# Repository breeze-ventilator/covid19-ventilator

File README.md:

#  Breeze Ventilator
Welcome to our open-source, low-cost ventilator design! We are a group of students, physicians and engineers who worked on the design to help alleviate the critical need for ventilators during the COVID-19 pandemic.

Here is a [video](https://youtu.be/5ufh_80dSsk) with an overview of our design.

<p align="center">
  
</p>

You can also check out our [in depth design video](https://youtu.be/dRpsoaCI0QA) and [public announcement video](https://youtu.be/4-jjhEgUjkQ).

## Operational Diagram

## Folder Structure
**Mechanical:** Everything you need to construct the device including the bill of materials and the CAD files.

**Software:** Breeze ventilator code including code for both the interface (running on the Raspberry Pi 4) and the firmware (running on the Arduino Mega).

**Electronics:** PCBs and the circuit diagrams.

**Documentation:** Documentation for operating the device including the User Guide and the Assembly guide, which will help you set-up and run your device smoothly.

## Conclusion

The Breeze Ventilator was built during a design sprint and is not ready to be safely used as a functioning ventilator. Nevertheless, we hope that you will find inspiration from our design and that it will help you with your projects! 

If you have any comments, questions or suggestions you can reach out to our team through raphael.hotter@mail.mcgill.ca

Good luck with your projects and happy creating!

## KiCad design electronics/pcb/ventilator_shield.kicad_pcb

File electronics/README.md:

# Electrical
* `pcb` folder contains KiCad files.
* `parts` folder contains datasheets of off-the-shelf parts.
* `Electrical diagram.pdf` is a simplified diagram of the electronics/
* `Diagram as sent for quote.pdf` is the diagram of the pcb as used.
* `Board Specifications.pdf` contains calculations for the design of the pcb

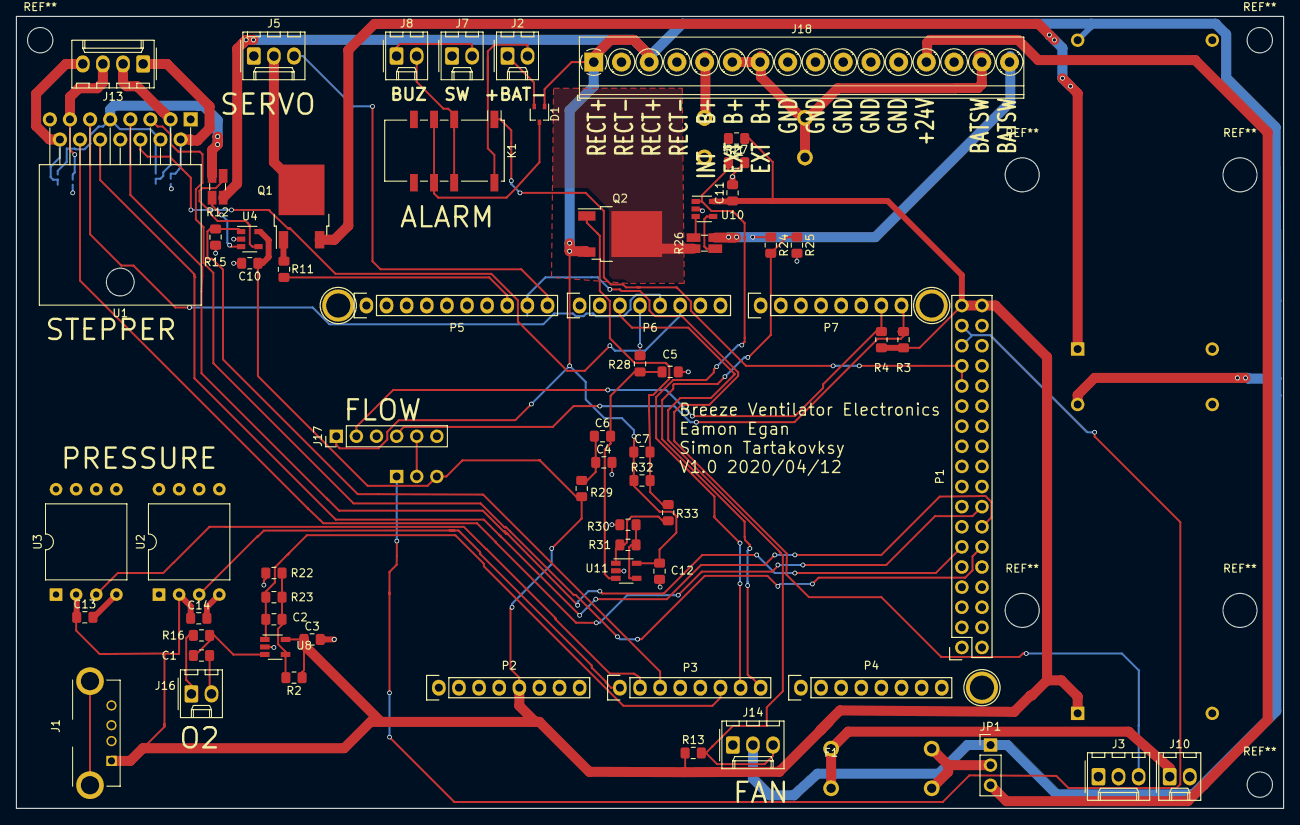
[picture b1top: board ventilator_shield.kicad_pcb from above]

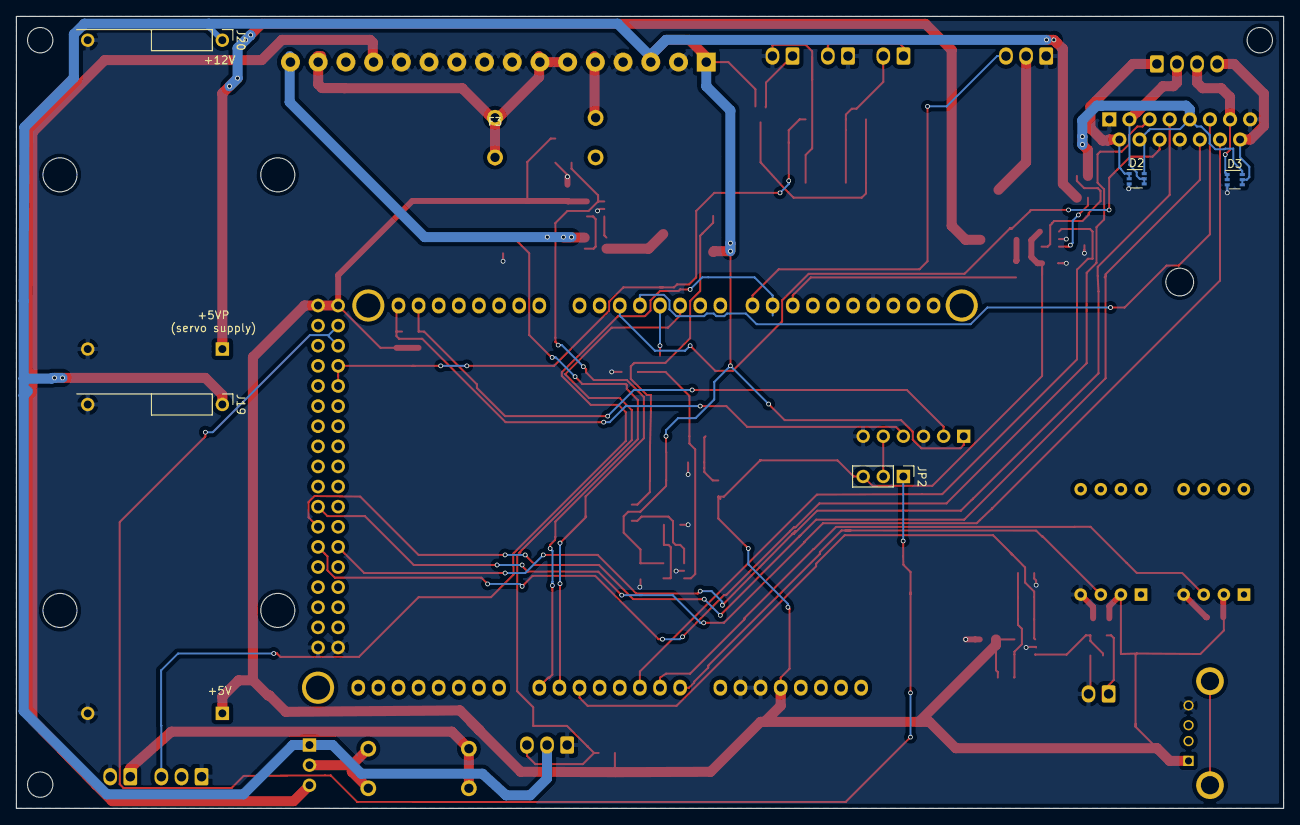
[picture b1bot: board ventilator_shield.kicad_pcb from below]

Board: 2 copper layers, 160.0 x 100.0 mm, 74 parts (6 on the bottom side), 56 nets.

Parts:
C1, C2, C3, C4, C5, C6, C7, C10, C11, C12, C13, C14: C; C_0805_2012Metric_Pad1.15x1.40mm_HandSolder
D1: BAV70W; SOT-323_SC-70
D2, D3: BAV756S; SOT-363_SC-70-6
F1, F3: Fuse; LittelFuse_clips_01110501Z_10mm_fuse
J1: USB_A; USB_A_TE_Connectivity_292303-1
J2, J7, J8, J10, J16: Conn_01x02; Molex_KK-254_AE-6410-02A_1x02_P2.54mm_Vertical
J3, J5, J14: Conn_01x03; Molex_KK-254_AE-6410-03A_1x03_P2.54mm_Vertical
J13: Conn_01x04; Molex_KK-254_AE-6410-04A_1x04_P2.54mm_Vertical
J17: Conn_01x06_Male; PinHeader_1x06_P2.54mm_Vertical
J18: Screw_Terminal_01x16; TerminalBlock_Phoenix_PT-1,5-16-3.5-H_1x16_P3.50mm_Horizont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
J19, J20: Conn_01x04; Buck_Converter_Module
JP1, JP2: Jumper_3_Open; PinHeader_1x03_P2.54mm_Vertical
K1: G6S-2; Relay_DPDT_Omron_G6S-2F
P1: Digital; Socket_Strip_Arduino_2x18
P2: Power; Socket_Strip_Arduino_1x08
P3, P4: Analog; Socket_Strip_Arduino_1x08
P5: PWM; Socket_Strip_Arduino_1x10
P6: PWM; Socket_Strip_Arduino_1x08
P7: Communication; Socket_Strip_Arduino_1x08
P10, P11, P13: CONN_01X01; Arduino_1pin
Q1, Q2: SUD19P06-60; TO-252-2
R1, R2, R11, R15, R16, R22, R23, R27: R_US; R_0805_2012Metric_Pad1.15x1.40mm_HandSolder
R3, R4: 4K7; R_0805_2012Metric_Pad1.15x1.40mm_HandSolder
R12, R26: LVK12R010FER; R_Shunt_Ohmite_LVK12
R13: 1K; R_0805_2012Metric_Pad1.15x1.40mm_HandSolder
R24, R28, R29, R31, R33: 20K; R_0805_2012Metric_Pad1.15x1.40mm_HandSolder
R25, R30, R32: 10K; R_0805_2012Metric_Pad1.15x1.40mm_HandSolder
U1: L298HN; TO-220-15_P2.54x2.54mm_StaggerOdd_Lead5.84mm_TabDown
U2, U3: HSCDLND001PGAA5; DIP-8_W13.3mm
U4, U10: INA138; SOT-23-5
U8, U11: OPA188xxDBV; TSOT-23-5

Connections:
+5V: C3.1, C10.1, C11.1, C13.1, C14.1, J1.1, J19.1, JP2.3, P1.35, P1.36, P2.5, R1.1, R2.1, R3.1, R4.1, R13.1, R29.2, U2.2, U3.2, U4.5, U8.5, U10.5
+5VP: J20.1, Q1.3
+12V: C7.1, C12.1, D1.1, J14.2, J17.1, J18.1, J18.3, J19.2, J20.2, JP1.1, Q2.3, R12.1, R32.1, U11.5
+24V: J18.13, JP1.3
/Sheet5E8D3A49/ALARM_OFF: K1.1, P1.27, P1.29
/Sheet5E8D3A49/ESC_PWM1: J3.3, P5.9
/Sheet5E8D3A49/EnA: P6.6, U1.6
/Sheet5E8D3A49/EnB: P6.5, U1.11
/Sheet5E8D3A49/FAN_TACH: J14.3, P6.3, R13.2
/Sheet5E8D3A49/IN1: P1.12, U1.5
/Sheet5E8D3A49/IN2: P1.11, U1.7
/Sheet5E8D3A49/IN3: P1.14, U1.10
/Sheet5E8D3A49/IN4: P1.16, U1.12
/Sheet5E8D3A49/SERVO_OFF: P5.8, R11.2
/Sheet5E8D3A49/SERVO_PWM1: J5.3, P5.10
/Sheet5E8D3A49/STEPPER_CURRENT: P3.3, R15.1, U4.1
/Sheet5E8D3A49/p_5: J5.2, Q1.2
/Sheet5E8D3A49/p_6: D2.1, D2.2, J13.1, U1.2
/Sheet5E8D3A49/p_7: D2.4, D2.5, J13.2, U1.3
/Sheet5E8D3A49/p_8: D3.1, D3.2, J13.3, U1.13
/Sheet5E8D3A49/p_9: D3.4, D3.5, J13.4, U1.14
/Sheet5E8D3A49/p_10: F1.2, JP1.2
/Sheet5E8D3A49/p_11: F1.1, J10.1
/Sheet5E8D3A49/p_13: D2.6, D3.6, R12.4, U1.4, U1.9
/Sheet5E9ADB54/FLOW-SCL: J17.4, P7.8, R3.2
/Sheet5E9ADB54/FLOW-SDA: J17.2, P7.7, R4.2
/Sheet5E9ADB54/FLOWSENSOR_POWER: JP2.1, P1.31, P1.33
/Sheet5E9ADB54/O2SENSOR_OUT: C2.1, P3.6, R23.1, U8.1
/Sheet5E9ADB54/PRESSURE_A: P3.1, U2.3
/Sheet5E9ADB54/PRESSURE_B: P3.2, U3.3
/Sheet5EAFE470/BATT_CHARGE_CTRL: P6.4, R28.2
/Sheet5EAFE470/p_1: F3.2, J18.5
/Sheet5EAFE470/p_2: F3.1, J18.6, J18.7, J18.15
/Sheet5EAFE470/p_3: J18.16, R24.1, R26.4
/Sheet5EAFE470/p_4: Q2.2, R26.1
/arduino_mega/BATMON_CUR: P3.7, R1.2, R27.1, U10.1
/arduino_mega/BATMON_VLT: P3.8, R24.2, R25.1
GND: C1.2, C3.2, C4.2, C5.2, C10.2, C11.2, C12.2, C13.2, C14.2, D2.3, D3.3, J1.4, J2.2, J3.1, J5.1, J7.1, J10.2, J14.1, J16.2, J17.3, J17.6, J18.2, J18.4, J18.8, J18.9, J18.10, J18.11, J18.12, J19.3, J19.4, J20.3, J20.4, K1.12, P1.1, P1.2, P2.6, P2.7, P5.4, R15.2, R22.2, R25.2, R27.2, R30.2, U1.1, U1.8, U1.15, U2.4, U3.4, U4.2, U8.2, U10.2, U11.2
unnamed: C1.1, R16.1, U8.3
unnamed: C2.2, R2.2, R22.1, R23.2, U8.4
unnamed: C4.1, C6.1, R29.1
unnamed: C5.1, C6.2, R28.1, U11.3
unnamed: C7.2, Q2.1, R32.2, R33.2
unnamed: D1.2, J2.1
unnamed: D1.3, K1.4, K1.9
unnamed: J7.2, J8.1
unnamed: J8.2, K1.3, K1.10
unnamed: J16.1, R16.2
unnamed: J17.5, JP2.2
unnamed: Q1.1, R11.1
unnamed: R12.2, U4.3
unnamed: R12.3, U4.4
unnamed: R26.2, U10.3
unnamed: R26.3, U10.4
unnamed: R30.1, R31.2, U11.4
unnamed: R31.1, R33.1, U11.1

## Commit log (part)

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2020-04-11 Arduio messager py initial
2020-04-11 Levels of Warning for FlexValueCards
2020-04-12 Things Change Colors with Alarms!
2020-04-12 Delete Alarm.jsx
    it was a proof of concept that accidentally got in oops
2020-04-12 removed mobiscroll, added mode feature and used harsh's parameterinputcustom
2020-04-12 resolved package lock merge conflicts
2020-04-12 Delete .npmrc
    No need for mobiscroll!
2020-04-12 all main pieces are in, just needs more testing
2020-04-12 Fixed alarm screen!
2020-04-12 can cycle between inhalation and exhalation
2020-04-12 Fixed alarm screen inputs!
2020-04-12 All primary firmware components have been completed (#33)
    * testing without arduino done
    * set default parameters
    * testing
    * a
    * test3
    * a
2020-04-12 Status Bar
2020-04-12 Format changes
2020-04-12 UI updates: reduce input size for screen cutoff and changed interface colors.
2020-04-12 Fixed onboarding screen UI and added power off button.
2020-04-12 initial test
2020-04-12 Removed power off button from PatientProfile.jsx
2020-04-12 serial comms works
2020-04-12 change number of readings
2020-04-12 socket change
2020-04-12 raffi changes
2020-04-12 socket round 3
2020-04-12 socket round 4
2020-04-12 socket round 5
2020-04-12 socket v7
2020-04-13 arduino messager changes
2020-04-13 small update
2020-04-13 button tests
2020-04-13 hide the initial flow
2020-04-13 Import test font
2020-04-13 refactor Vitals, temporarily removed modals
2020-04-13 Added python scripts
2020-04-13 removed serialport dependency
2020-04-13 Removed serial port usage (#44)
    This will allow us to finally test on the Pi easily
2020-04-13 bugfix with merge
2020-04-13 show data, animate breathing
2020-04-13 add respiratory rate to main card
2020-04-14 Updated parameters and alarms UI!
2020-04-14 added clickable nav bar
2020-04-14 deleted nav bar
2020-04-14 Nav bar/alarm page UI updates
2020-04-14 some work
2020-04-14 Updated navigation bar UI!
2020-04-14 Added react-moment dependency
2020-04-14 Added sample data listener
2020-04-14 constants
2020-04-14 added recommended vals, colors
2020-04-14 Constants file updated as well as App.jsx cleaner
2020-04-14 Removed log
2020-04-14 Removed comment
2020-04-14 dunno
2020-04-14 Sample listener changes
2020-04-14 adapt styles to edit mode
2020-04-14 edit logic and styling
2020-04-14 full pipeline working
2020-04-14 Full pipeline working!! (#53)
2020-04-14 make increment functional, style changes
2020-04-14 keep values within range
2020-04-14 Quickly fixing unit alignment g Please enter the commit message for your changes. Lines starting
2020-04-14 propagate recommended values
2020-04-15 Added the patient profile button back in Please enter the commit message for your changes. Lines starting
2020-04-15 changed toggle for modes
2020-04-15 added recommended ranges
2020-04-15 Uodated patient onboarding modal / alarms aesthetic
2020-04-15 Updates to onboarding modal aesthetic
2020-04-15 respiratory rate + minute ventilation showing
2020-04-15 Change patient profile button color
2020-04-15 dropdown
2020-04-15 flow triggering works
2020-04-15 pressure support mode working
2020-04-15 donezo
2020-04-15 pressure support working
2020-04-15 removed unnecessary files
2020-04-15 flow sensor readings
2020-04-15 changed flow reading frequency to 500
2020-04-15 some minor edits
2020-04-15 more fixes
2020-04-15 some air intake stuff
2020-04-15 ALARMS RING
2020-04-15 new ranges
2020-04-15 response to code review
2020-04-15 added power/standby button
2020-04-15 Revert "added power/standby button"
2020-04-15 Revert "added power/standby button" (#62)
2020-04-15 Revert "dropdown"
2020-04-15 Revert "dropdown" (#63)
2020-04-15 changed sensitivity param sending
2020-04-15 patient profile button change
2020-04-15 Finished standby
2020-04-15 uncommented picomms + changed pressure to float
2020-04-15 Completed standby
2020-04-15 oxygen sensor
2020-04-15 oxygen controller
2020-04-15 full screen automatically
2020-04-16 did the thing raffi said
2020-04-16 fixed electron bug
2020-04-16 firmware
2020-04-16 socketio bug fix
2020-04-16 bug?
2020-04-16 bug fix?
2020-04-16 bug fix
2020-04-16 custom step sizes
2020-04-16 custom step sizes (#67)
2020-04-16 alarm units and input fix
2020-04-16 alarm units and input fix (#68)
2020-04-19 not sure what this commit is
2020-04-19 testing
2020-04-20 comm working on mac
2020-04-20 added electron prebuilt compile to dev dependencies
2020-04-20 removed
2020-04-20 changed port
2020-04-20 get_ports
2020-04-20 fixed bug
2020-04-20 nonsense
2020-04-20 fixed?
2020-04-20 other port
2020-04-20 EVERYTHING IS GONE
2020-04-20 added pyshell
2020-04-20 maybe?
2020-04-20 webpack fix
2020-04-20 window require
2020-04-20 working i hope
2020-04-20 serial port name
2020-04-20 fixed pyshell maybe
2020-04-20 serial change
2020-04-20 working on mac maybe
2020-04-20 kp change
2020-04-20 removed zip
2020-04-20 new code
2020-04-21 new changes
2020-04-21 removed tests
2020-04-21 changed serial
2020-04-21 hopefully working
2020-04-21 initialize blower
2020-04-21 ports
2020-04-21 changed rates
2020-04-21 firmware 5
2020-04-21 firmware update on new hardware
2020-04-21 masters firmware
2020-04-21 changed minute ventilation alarm display
2020-04-21 test 1
2020-04-21 test 2
2020-04-21 increased blower max speed
2020-04-21 lowered Kp to 3
2020-04-21 test 3
2020-04-21 new change
2020-04-21 test
2020-04-21 printing set pressure
2020-04-21 hopefully functional
2020-04-21 changed
2020-04-21 tune
2020-04-21 guess
2020-04-21 simple code
2020-04-21 battery set to 5 A
2020-04-21 battery
2020-04-21 current
2020-04-22 ready for tomorrow
2020-04-22 code on comp
2020-04-24 Create LICENSE (#74)
2020-04-26 refactoring
2020-04-27 changed battery charging to 1 amp
2020-04-27 printing pressure
2020-04-27 removed battery printing
2020-04-27 added flow printing
2020-04-27 pressure sensor transfer function update
2020-04-27 pressure printing firmware
2020-04-28 removed rise time hack
2020-04-28 changed pid values
2020-04-28 pid tuning + removed rise time hack
2020-04-28 Firmware update: (#84)
    * test 2
    * lowered Kp to 3
    * test 3
    * test
    * printing set pressure
    * b
2020-04-28 switch to test mode
2020-04-28 added printing option
2020-04-29 o2 progress
2020-04-29 progress
2020-04-29 adjusted start sequence for blower
2020-04-29 pressure printing
2020-04-29 progress' '
2020-04-29 quiet on standby
2020-04-29 oxygen sensor prototype code done
2020-04-29 readjusted start sequence
2020-04-29 air controller prototype complete
2020-04-29 sending min & max pressure
2020-04-29 added patient disconnection option
2020-04-29 propagate alarm setting changes
2020-04-29 workaround for pressure, change defaults and messages
2020-04-29 re-insert test data sampler
2020-04-29 re-insert sounds
2020-04-29 firmware: ESC blower startup fix
2020-04-29 charges during delays and at startup
2020-04-29 added init
2020-04-29 blower PID
2020-04-29 increased to 120
2020-04-29 progress'
2020-04-30 oxygen code
2020-04-30 o2 merge
2020-04-30 firmware update: oxygen control code (#89)
2020-04-30 no alarm when values are null
2020-04-30 proper direction
2020-04-30 firmware: changed zeroing method
2020-04-30 firmware update: added header file for oxygen stepper
2020-04-30 air control
2020-04-30 firmware update: air valve (#90)
2020-04-30 firmware update: battery control + allow higher output on blower
2020-04-30 fixed import of absolute path
2020-04-30 workaround for alarms on prod (#91)
2020-04-30 firmware update: standby mode
2020-04-30 add SRC
2020-04-30 copywebpackplugin
2020-04-30 alarm sound works
2020-04-30 Alarm plays sound on build (#92)
2020-04-30 firmware: send min & max pressure to pi for alarms (#85)
2020-04-30 final working firmware
2020-08-04 Added mech
2020-08-04 added youtube thubnail
2020-08-04 moved software files to software folder
2020-08-04 Revert "moved software files to software folder"
    This reverts commit 884aea9a637e06952afbf89b7f2d055115802bd4.
2020-08-04 Bump electron from 8.2.1 to 8.2.4 in /interface/breeze-electron
    Bumps [electron](https://github.com/electron/electron) from 8.2.1 to 8.2.4.
    - [Release notes](https://github.com/electron/electron/releases)
    - [Changelog](https://github.com/electron/electron/blob/master/docs/breaking-changes.md)
    - [Commits](https://github.com/electron/electron/compare/v8.2.1...v8.2.4)
2020-08-04 moved software to software folder
2020-08-04 Bump electron from 8.2.1 to 8.2.4 in /software/interface/breeze-electron
    Bumps [electron](https://github.com/electron/electron) from 8.2.1 to 8.2.4.
    - [Release notes](https://github.com/electron/electron/releases)
    - [Changelog](https://github.com/electron/electron/blob/master/docs/breaking-changes.md)
    - [Commits](https://github.com/electron/electron/compare/v8.2.1...v8.2.4)
2020-08-04 smaller mech
    smaller version
2020-08-04 Revert "Merge branch 'master' of https://github.com/Open-Breeze/covid19-ventilator"
    This reverts commit ee1fc334d0edb1cdaf5cae68c4c636bee8a0c7b8, reversing
    changes made to 8e019810db8a1fb51a5d3eb0c47973fbc761a7c8.
2020-08-04 mechanical readme
2020-08-04 moved documentation to folder
2020-08-04 Bump electron from 8.2.1 to 8.2.4 in /software/interface/breeze-electron (#94)
    Bumps [electron](https://github.com/electron/electron) from 8.2.1 to 8.2.4.
    - [Release notes](https://github.com/electron/electron/releases)
    - [Changelog](https://github.com/electron/electron/blob/master/docs/breaking-changes.md)
    - [Commits](https://github.com/electron/electron/compare/v8.2.1...v8.2.4)
2020-08-04 added pcbs
2020-08-04 cleaned electronics
2020-08-04 cleaning or smthing
2020-08-05 Add files via upload
    Added block diagram
2020-08-10 added grab cad link
2020-10-06 Bump electron from 8.2.4 to 8.5.1 in /software/interface/breeze-electron
    Bumps [electron](https://github.com/electron/electron) from 8.2.4 to 8.5.1.
    - [Release notes](https://github.com/electron/electron/releases)
    - [Changelog](https://github.com/electron/electron/blob/master/docs/breaking-changes.md)
    - [Commits](https://github.com/electron/electron/compare/v8.2.4...v8.5.1)
2020-10-06 Bump electron from 8.2.4 to 8.5.2 in /software/interface/breeze-electron
    Bumps [electron](https://github.com/electron/electron) from 8.2.4 to 8.5.2.
    - [Release notes](https://github.com/electron/electron/releases)
    - [Changelog](https://github.com/electron/electron/blob/master/docs/breaking-changes.md)
    - [Commits](https://github.com/electron/electron/compare/v8.2.4...v8.5.2)
2021-01-28 Bump electron from 8.2.4 to 9.4.0 in /software/interface/breeze-electron
    Bumps [electron](https://github.com/electron/electron) from 8.2.4 to 9.4.0.
    - [Release notes](https://github.com/electron/electron/releases)
    - [Changelog](https://github.com/electron/electron/blob/master/docs/breaking-changes.md)
    - [Commits](https://github.com/electron/electron/compare/v8.2.4...v9.4.0)
2021-10-12 Bump electron in /software/interface/breeze-electron
    Bumps [electron](https://github.com/electron/electron) from 8.2.4 to 11.5.0.
    - [Release notes](https://github.com/electron/electron/releases)
    - [Changelog](https://github.com/electron/electron/blob/main/docs/breaking-changes.md)
    - [Commits](https://github.com/electron/electron/compare/v8.2.4...v11.5.0)
    ---
    updated-dependencies:
2022-03-25 Bump electron in /software/interface/breeze-electron
    Bumps [electron](https://github.com/electron/electron) from 8.2.4 to 13.6.6.
    - [Release notes](https://github.com/electron/electron/releases)
    - [Changelog](https://github.com/electron/electron/blob/main/docs/breaking-changes.md)
    - [Commits](https://github.com/electron/electron/compare/v8.2.4...v13.6.6)
    ---
    updated-dependencies:
